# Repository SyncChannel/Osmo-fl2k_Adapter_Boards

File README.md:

# SMA Adapter Boards for Osmo-fl2k

Three channel Software Defined Radio (SDR) transmitter using USB to VGA adapters with the FL2000 chipset.

Check out my blog to get full details on these boards.

http://syncchannel.blogspot.com

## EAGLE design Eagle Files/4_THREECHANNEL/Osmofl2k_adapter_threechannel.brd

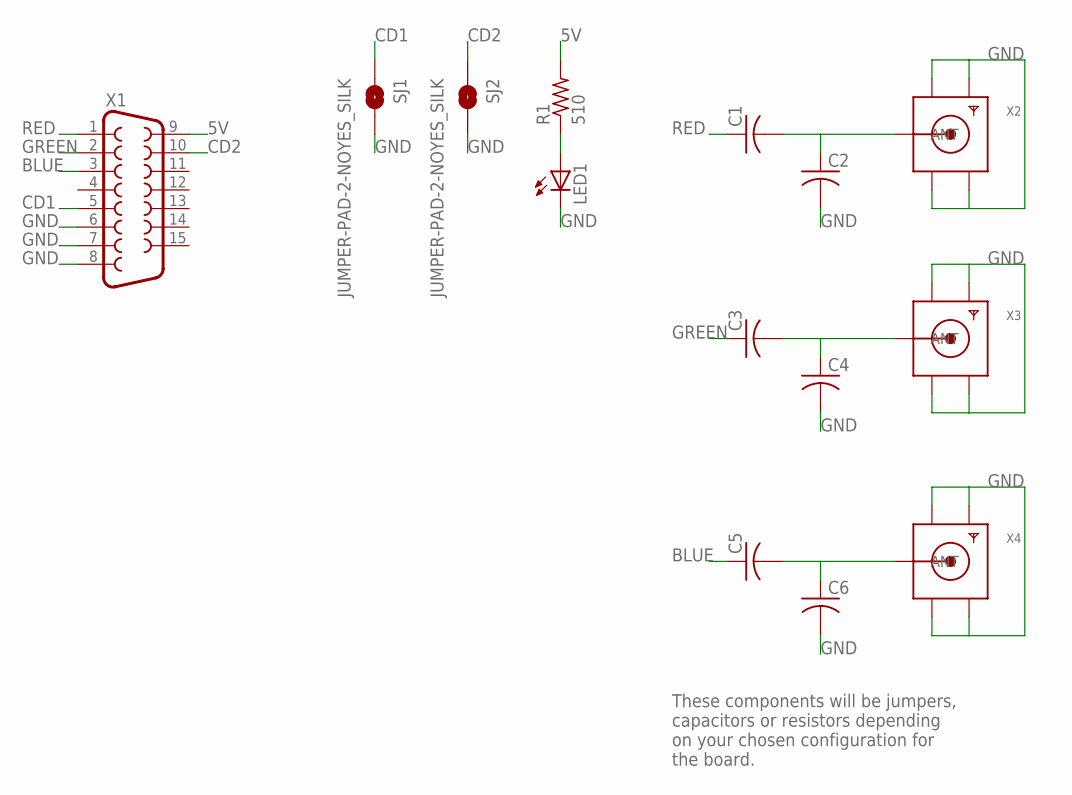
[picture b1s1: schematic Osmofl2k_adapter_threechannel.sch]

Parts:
C1, C2, C3, C4, C5, C6: C-USC0603; C0603
LED1: LEDCHIPLED_0805; CHIPLED_0805
R1: 510; R0805
SJ1, SJ2: JUMPER-PAD-2-NOYES_SILK; PAD-JUMPER-2-NO_YES_SILK
X1: F15HDH; HDF15H
X2, X3, X4: SMACONNECTOR_EDGE; SMA_EDGELAUNCH

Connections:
5V: R1.2, X1.9
BLUE: C5.1, X1.3
CD1: SJ1.1, X1.5
CD2: SJ2.1, X1.10
GND: C2.2, C4.2, C6.2, LED1.C, SJ1.2, SJ2.2, X1.6, X1.7, X1.8, X2.GND@1 (GND4), X2.GND@2 (GND3), X2.GND@3 (GND2), X2.GND@4 (GND1), X3.GND@1 (GND4), X3.GND@2 (GND3), X3.GND@3 (GND2), X3.GND@4 (GND1), X4.GND@1 (GND4), X4.GND@2 (GND3), X4.GND@3 (GND2), X4.GND@4 (GND1)
GREEN: C3.1, X1.2
unnamed: C1.2, C2.1, X2.P (ANT)
unnamed: LED1.A, R1.1
unnamed: C3.2, C4.1, X3.P (ANT)
unnamed: C5.2, C6.1, X4.P (ANT)
RED: C1.1, X1.1

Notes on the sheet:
These components will be jumpers, capacitors or resistors depending on your chosen configuration for the board.

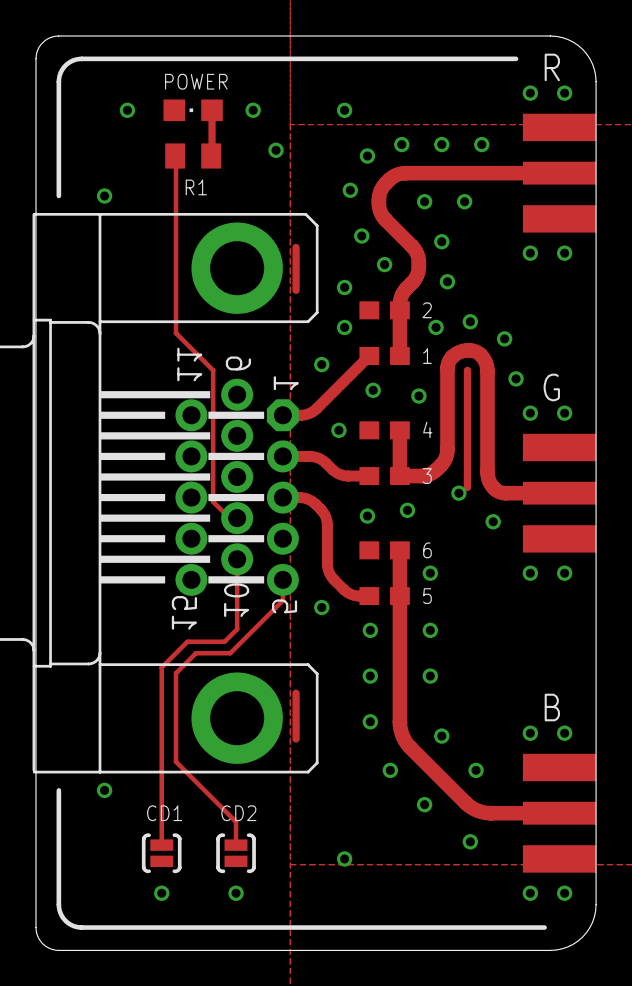
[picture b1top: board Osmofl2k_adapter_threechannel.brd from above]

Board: 2 copper layers, 31.1 x 50.8 mm, 14 parts (1 on the bottom side), 11 nets.

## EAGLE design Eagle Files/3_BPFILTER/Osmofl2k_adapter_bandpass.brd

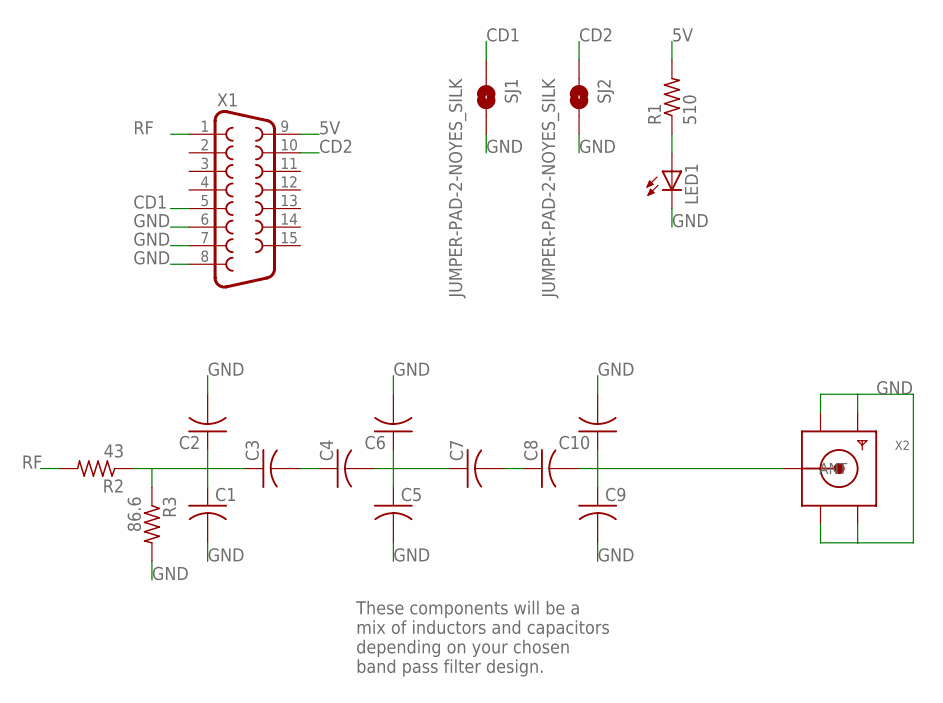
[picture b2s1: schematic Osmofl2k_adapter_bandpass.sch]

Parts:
C1, C4, C5, C8, C9: C-USC0603; C0603
C2, C6, C10: C-USC0402; C0402
C3, C7: C-USC0805; C0805
LED1: LEDCHIPLED_0805; CHIPLED_0805
R1: 510; R0805
R2: 43; R0805
R3: 86.6; R0805
SJ1, SJ2: JUMPER-PAD-2-NOYES_SILK; PAD-JUMPER-2-NO_YES_SILK
X1: F15HDH; HDF15H
X2: SMACONNECTOR_EDGE; SMA_EDGELAUNCH

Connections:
5V: R1.2, X1.9
CD1: SJ1.1, X1.5
CD2: SJ2.1, X1.10
GND: C1.2, C2.2, C5.2, C6.2, C9.2, C10.2, LED1.C, R3.2, SJ1.2, SJ2.2, X1.6, X1.7, X1.8, X2.GND@1 (GND4), X2.GND@2 (GND3), X2.GND@3 (GND2), X2.GND@4 (GND1)
unnamed: C4.2, C5.1, C6.1, C7.1
unnamed: LED1.A, R1.1
unnamed: C3.2, C4.1
unnamed: C1.1, C2.1, C3.1, R2.1, R3.1
unnamed: C7.2, C8.1
unnamed: C8.2, C9.1, C10.1, X2.P (ANT)
RF: R2.2, X1.1

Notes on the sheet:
These components will be a mix of inductors and capacitors depending on your chosen band pass filter design.

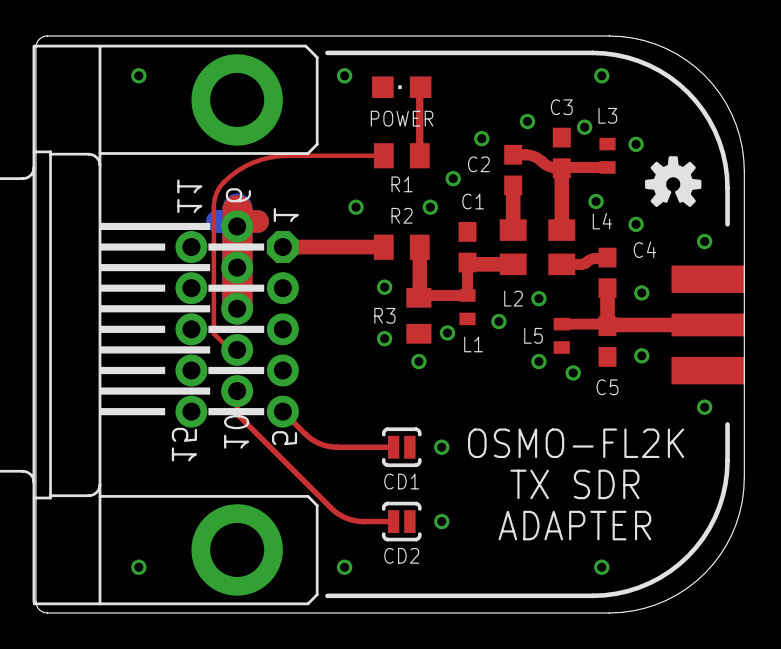
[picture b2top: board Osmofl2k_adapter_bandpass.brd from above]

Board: 2 copper layers, 39.4 x 32.1 mm, 19 parts (1 on the bottom side), 11 nets.

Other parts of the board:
U$1: OSHW-LOGO-S

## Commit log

2018-05-28 Initial upload.
    Upload PCB files.

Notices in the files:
parts and their libraries:
SparkFun-Passives: Licensing: Creative Commons ShareAlike 4.0 International - https://creativecommons.org/licenses/by-sa/4.0
